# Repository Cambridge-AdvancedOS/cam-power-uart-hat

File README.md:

# Raspberry Pi Serial and Power Switching Hat

A Raspberry Pi Hat that provides USB serial access to the Pi's serial console. It allows for both power injection and switching via a JST-XH connector. There is also a combo temperature sensor/eeprom that can be accessed over USB.

Created for the [L41 Advanced Operating Systems](https://www.cl.cam.ac.uk/teaching/2021/L41/) course at UCAM CST.

## Board Details

### Notable ICs
* [MCP2221A](./docs/mcp2221a.pdf) - USB UART Interface chip, provides USB communications, GPIO control used for status LEDs and the power switching, and I2C interfacing to control the temperature sensor/eeprom.
* [MCP98243](./docs/mcp98243.pdf) - I2C temperature sensor and eeprom chip accessible via the MCP2221A. Could be substituted for other I2C chips as long as the power/GND and I2C pins match.
* [RQ5C060BC](./docs/rq5c060bc.pdf) - High power Pch MOSFET, can be substituted for any other high power (min 3A) MOSFET with a low gate threshold (must fully activate at Vgs = 3v3) and a GSD pin arrangement.

### Connectors
* Micro USB - Provides USB data and can provide power to the onboard ICs in the absense of the JST connector. No power is passed forward to the RPi however, so it cannot be powered from a single USB cable.
* [JST-XH](./docs/jst-xh.pdf) - Main power supply for the RPi, cables should be fitted with XHP-2 connectors with +ve on pin 1 and -ve on pin 2.
* RPi connector - Fits to the top end of the RPi GPIO header, uses a minimum of pins and leaves the remainder for other interaction.

## License

Designed by Thomas Bytheway for University of Cambridge.

Schematic details inspired by:
### [Adafruit-MCP2221](https://github.com/adafruit/Adafruit-MCP2221-PCB)
Designed by Limor Fried/Ladyada for Adafruit Industries.

### [Adafruit-PiUART](https://github.com/adafruit/Adafruit-PiUART-PCB)
Designed by Limor Fried/Ladyada for Adafruit Industries.

Creative Commons Attribution/Share-Alike, all text above must be included in any redistribution. See license.txt for additional details.

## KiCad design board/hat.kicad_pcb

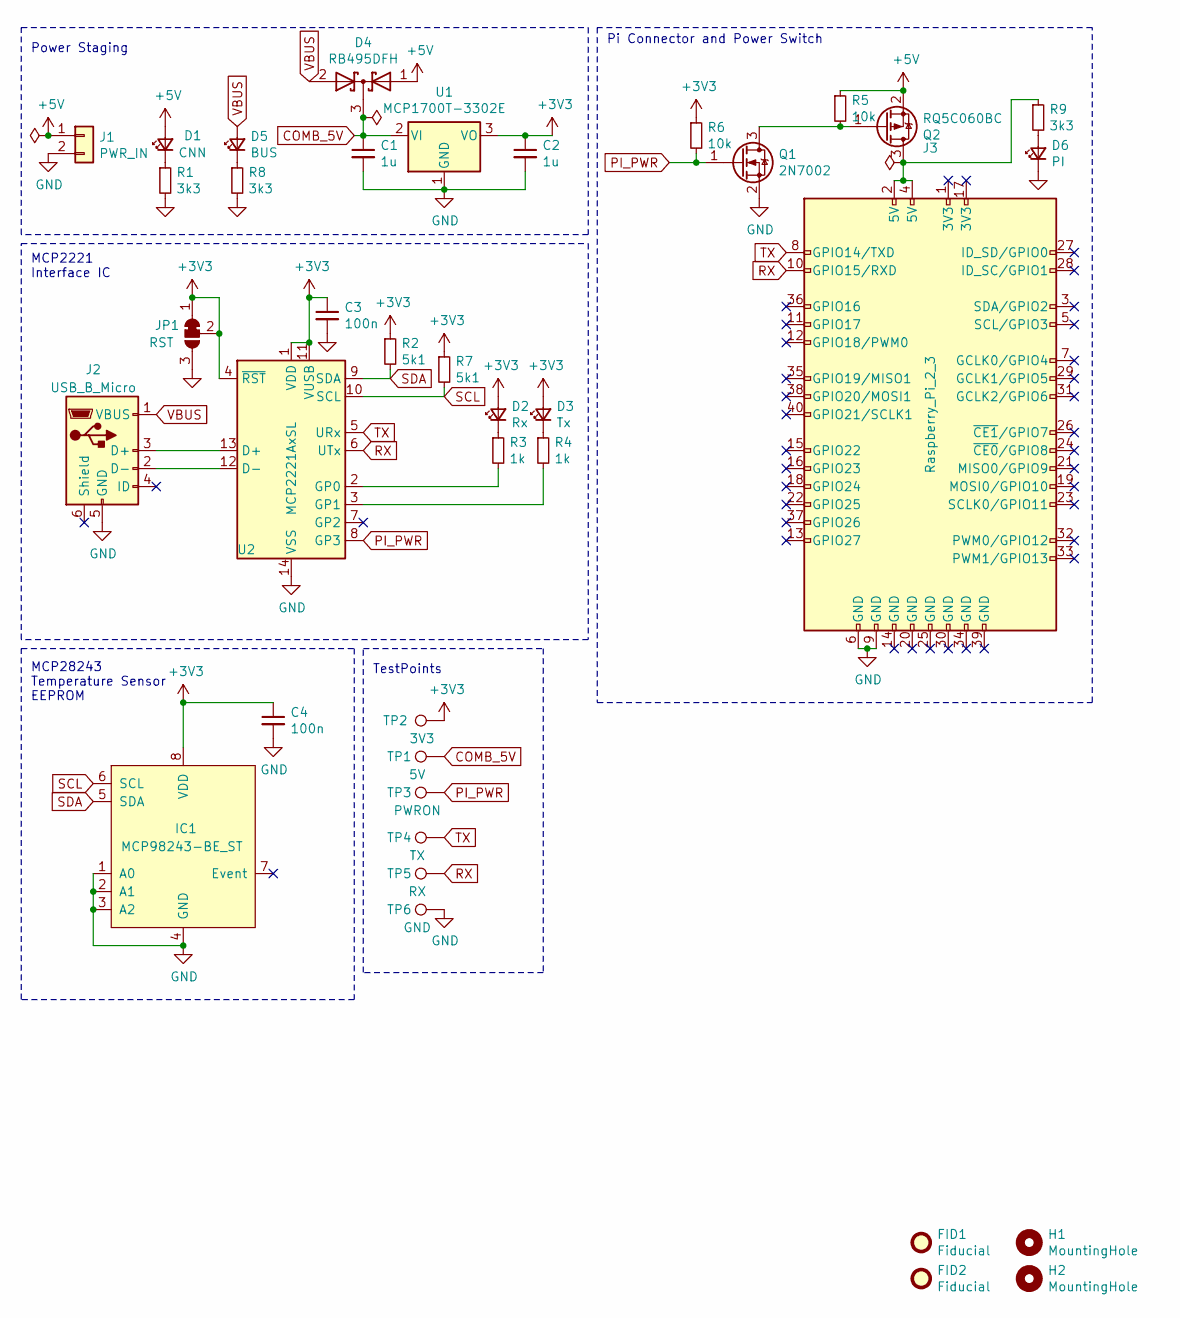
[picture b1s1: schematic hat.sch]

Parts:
C1, C2: 1u; C_0603_1608Metric
C3, C4: 100n; C_0603_1608Metric
D1: CNN; LED_0805_2012Metric; Farnell 2610416
D2: Rx; LED_0805_2012Metric; Farnell 2610419
D3: Tx; LED_0805_2012Metric; Farnell 2610420
D4: RB495DFH; SC-59; Farnell 2772677
D5: BUS; LED_0805_2012Metric; Farnell 2610416
D6: PI; LED_0805_2012Metric; Farnell 2610416
FID1, FID2: Fiducial; Fiducial_0.75mm_Mask1.5mm
H1, H2: MountingHole; MountingHole_2.7mm_M2.5
IC1: MCP98243-BE_ST; TSSOP-8_4.4x3mm_P0.65mm; Mouser 579-MCP98243-BE/ST
J1: PWR_IN; JST_XH_S2B-XH-A-1_1x02_P2.50mm_Horizontal; Farnell 1516289
J2: USB_B_Micro; USB_Micro-B_Molex-105017-0001; Farnell 2293836
J3: Raspberry_Pi_2_3; Samtec_HLE-105-02-xxx-DV-BE-A_2x05_P2.54mm_Horizontal; Mouser 200-HLE1052SDVBEAKTR
JP1: RST; PinHeader_1x03_P1.27mm_Vertical
Q1: 2N7002; SOT-23; Farnell 1713823
Q2: RQ5C060BC; SOT-23; Farnell 2706766
R1, R8, R9: 3k3; R_0603_1608Metric
R2, R7: 5k1; R_0603_1608Metric; Farnell 2447404
R3, R4: 1k; R_0603_1608Metric
R5, R6: 10k; R_0603_1608Metric
TP1: 5V; TestPoint_THTPad_1.5x1.5mm_Drill0.7mm
TP2: 3V3; TestPoint_THTPad_1.5x1.5mm_Drill0.7mm
TP3: PWRON; TestPoint_THTPad_1.5x1.5mm_Drill0.7mm
TP4: TX; TestPoint_THTPad_1.5x1.5mm_Drill0.7mm
TP5: RX; TestPoint_THTPad_1.5x1.5mm_Drill0.7mm
TP6: GND; TestPoint_THTPad_1.5x1.5mm_Drill0.7mm
U1: MCP1700T-3302E; SOT-89-3; Farnell 1439380
U2: MCP2221AxSL; SOIC-14_3.9x8.7mm_P1.27mm; Farnell 2678460

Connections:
+3V3: C2.1, C3.1, C4.1, D2.2 (A), D3.2 (A), IC1.8 (VDD), JP1.1 (A), JP1.2 (C), R2.1, R6.1, R7.1, TP2.1, U1.3 (VO), U2.1 (VDD), U2.4 (~RST), U2.11 (VUSB)
+5V: D1.2 (A), D4.1 (A), J1.1, Q2.2 (S), R5.1
COMB_5V: C1.1, D4.3 (K), TP1.1, U1.2 (VI)
GND: C1.2, C2.2, C3.2, C4.2, D6.1 (K), IC1.1 (A0), IC1.2 (A1), IC1.3 (A2), IC1.4 (GND), J1.2, J2.5 (GND), J3.6 (GND), J3.9 (GND), JP1.3 (B), Q1.2 (S), R1.2, R8.2, TP6.1, U1.1 (GND), U2.14 (VSS)
unnamed: D1.1 (K), R1.1
unnamed: D2.1 (K), R3.1
unnamed: D3.1 (K), R4.1
unnamed: D5.1 (K), R8.1
unnamed: D6.2 (A), R9.2
unnamed: J2.2 (D-), U2.12 (D-)
unnamed: J2.3 (D+), U2.13 (D+)
unnamed: J3.2 (5V), J3.4 (5V), Q2.3 (D), R9.1
unnamed: Q1.3 (D), Q2.1 (G), R5.2
unnamed: R3.2, U2.2 (GP0)
unnamed: R4.2, U2.3 (GP1)
PI_PWR: Q1.1 (G), R6.2, TP3.1, U2.8 (GP3)
RX: J3.10 (GPIO15/RXD), TP5.1, U2.6 (UTx)
SCL: IC1.6 (SCL), R7.2, U2.10 (SCL)
SDA: IC1.5 (SDA), R2.2, U2.9 (SDA)
TX: J3.8 (GPIO14/TXD), TP4.1, U2.5 (URx)
VBUS: D4.2 (A), D5.2 (A), J2.1 (VBUS)

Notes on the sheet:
Pi Connector and Power Switch
Power Staging
MCP2221 Interface IC
MCP28243 Temperature Sensor EEPROM
TestPoints

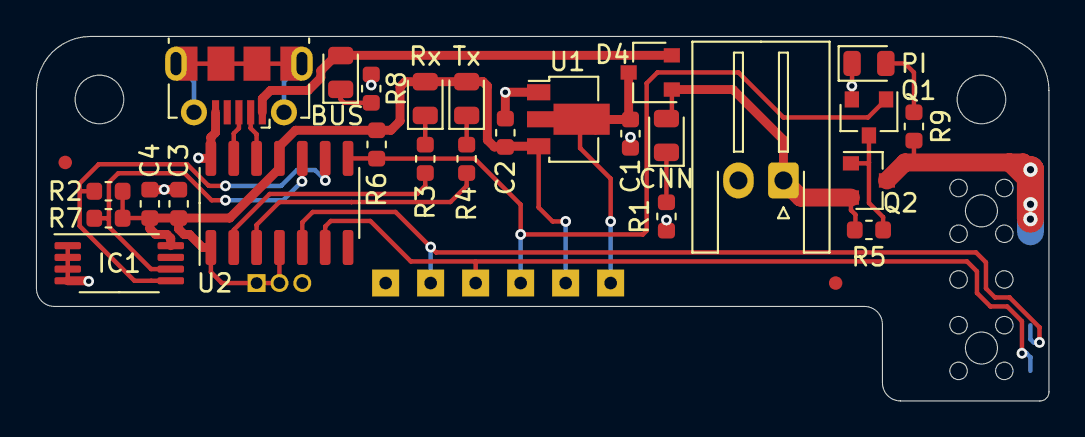
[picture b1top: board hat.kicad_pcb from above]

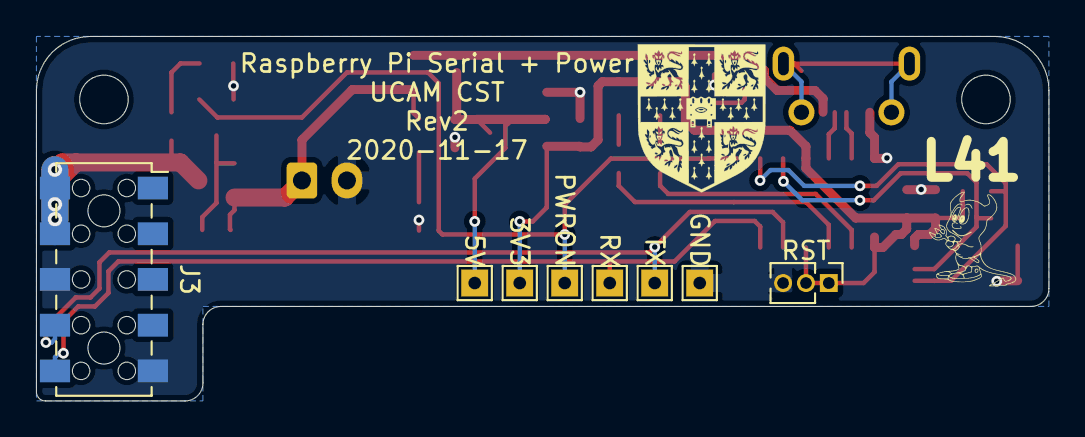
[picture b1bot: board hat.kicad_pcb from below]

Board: 2 copper layers, 56.2 x 20.2 mm, 38 parts (8 on the bottom side), 21 nets.

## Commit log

2021-04-22 Initial
2022-01-14 Add photos for README
2022-01-18 Added info to readme and copies of datasheets
